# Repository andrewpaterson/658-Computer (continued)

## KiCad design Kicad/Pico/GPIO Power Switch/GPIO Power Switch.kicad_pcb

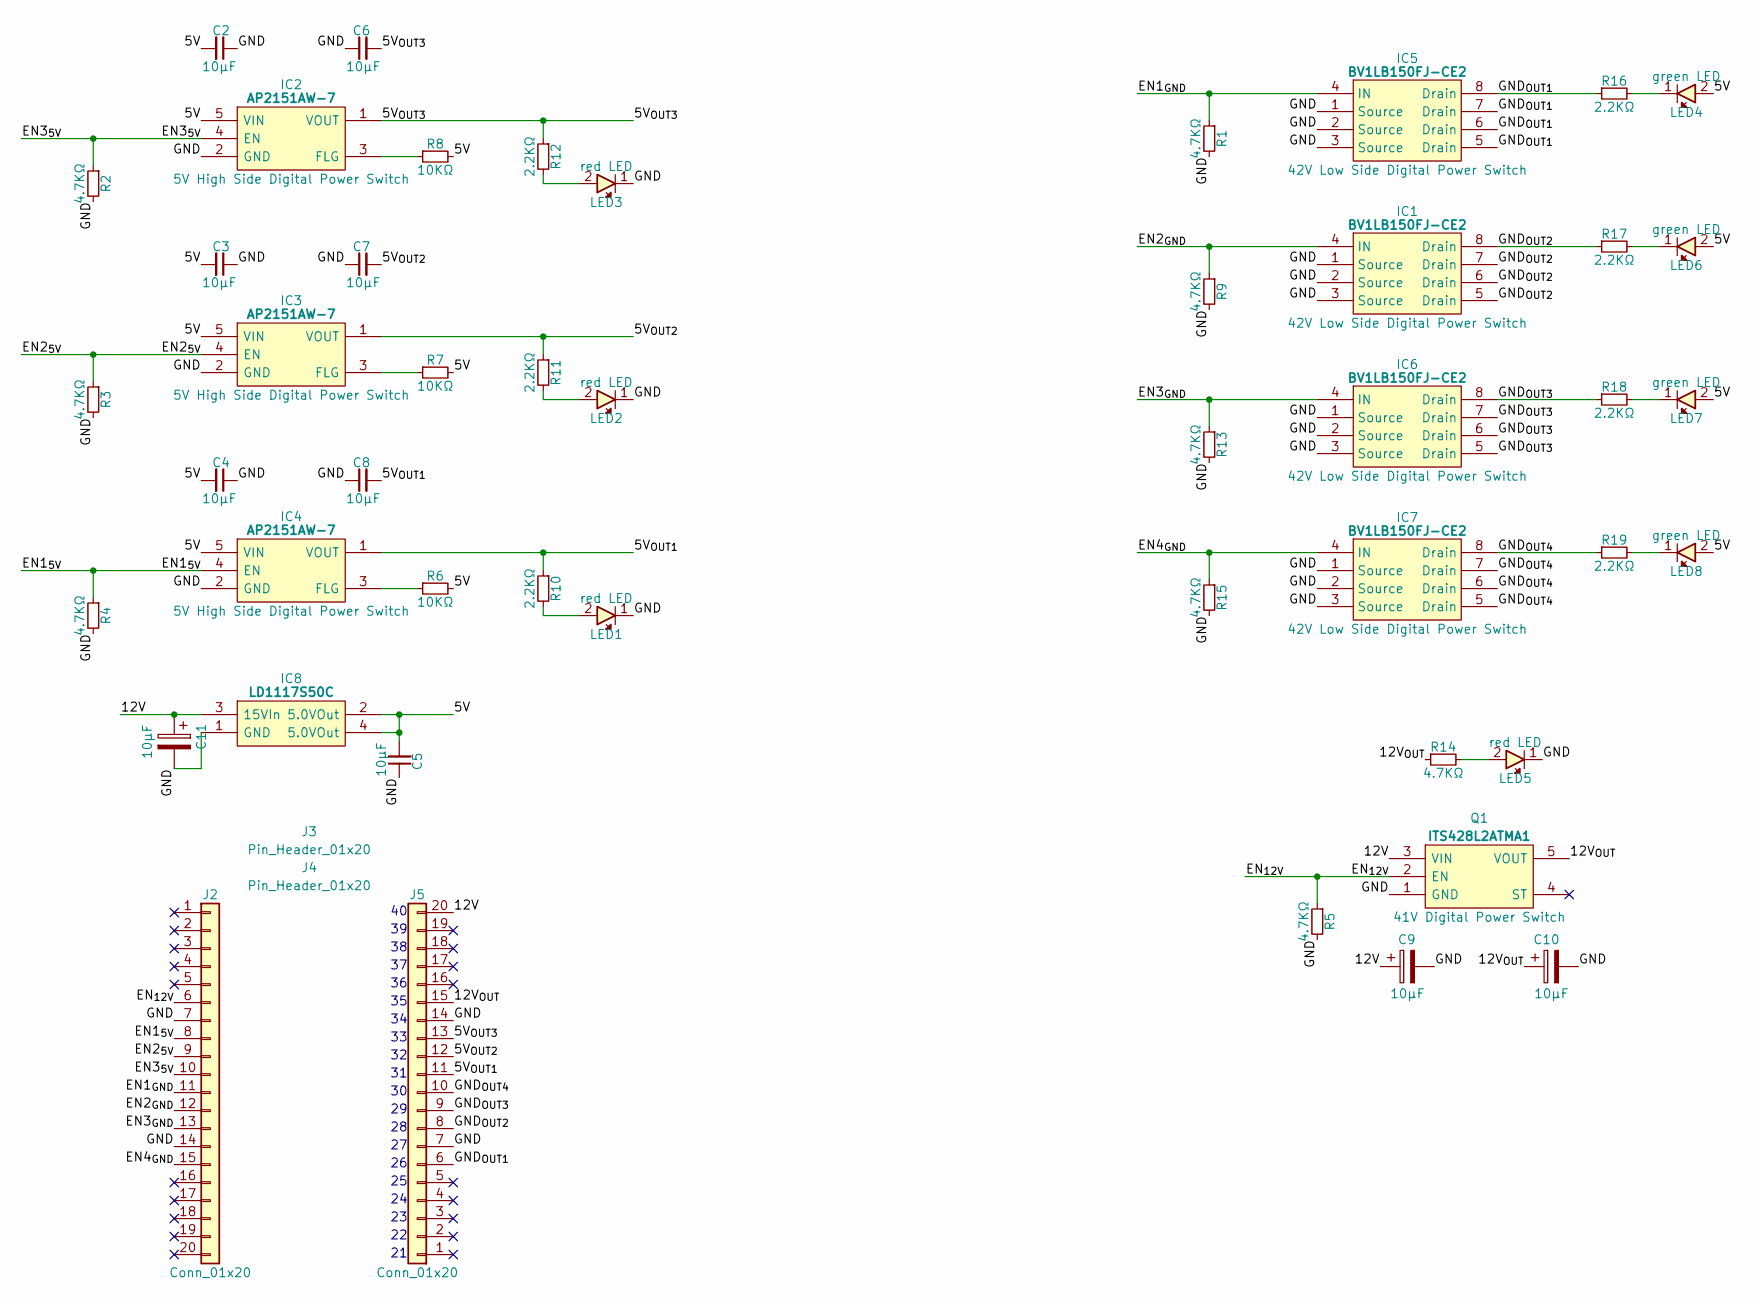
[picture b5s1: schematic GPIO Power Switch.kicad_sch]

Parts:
C2, C3, C4, C5, C6, C7, C8: 10μF; C_0805
C9, C10, C11: 10μF; CP_Radial_D4.0mm_P2.00mm
IC1, IC5, IC6, IC7: BV1LB150FJ-CE2; SOIC127P600X165-8N; Manufacturer_Part_Number BV1LB150FJ-CE2; Mouser Part Number 755-BV1LB150FJ-CE2
IC2, IC3, IC4: AP2151AW-7; SOT95P285X130-5N; Manufacturer_Part_Number AP2151AW-7; Mouser Part Number 621-AP2151AW-7
IC8: LD1117S50C; LD1117S33C; Manufacturer_Part_Number LD1117S50C
J2, J5: Conn_01x20; SIP_20_Pins
J3, J4: Pin_Header_01x20; PinHeader_1x20_P2.54mm_Vertical
LED1, LED2, LED3, LED5: 150224SS73100; 150224SS73100A; Manufacturer_Part_Number 150224SS73100; Mouser Part Number 710-150224SS73100
LED4, LED6, LED7, LED8: 150224VS73100A; Manufacturer_Part_Number 150224VS73100A; Mouser Part Number 710-150224VS73100A
Q1: ITS428L2ATMA1; Manufacturer_Part_Number ITS428L2ATMA1; Mouser Part Number 726-ITS428L2ATMA1
R1, R2, R3, R4, R5, R9, R13, R14, R15: 4.7KΩ; R_0805
R6, R7, R8: 10KΩ; R_0805
R10, R11, R12, R16, R17, R18, R19: 2.2KΩ; R_0805

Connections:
/5V: C2.2, C3.2, C4.2, C5.2, IC2.5 (VIN), IC3.5 (VIN), IC4.5 (VIN), IC8.2 (5.0VOut), IC8.4 (5.0VOut), LED4.2, LED6.2, LED7.2, LED8.2, R6.2, R7.2, R8.2
/5V_{OUT1}: C8.2, IC4.1 (VOUT), J5.11, R10.1
/5V_{OUT2}: C7.2, IC3.1 (VOUT), J5.12, R11.1
/5V_{OUT3}: C6.2, IC2.1 (VOUT), J5.13, R12.1
/12V: C9.1, C11.1, IC8.3 (15VIn), J5.20, Q1.3 (VIN)
/12V_{OUT}: C10.1, J5.15, Q1.5 (VOUT), R14.1
/EN1_{5V}: IC4.4 (EN), J2.8, R4.1
/EN1_{GND}: IC5.4 (IN), J2.11, R1.1
/EN2_{5V}: IC3.4 (EN), J2.9, R3.1
/EN2_{GND}: IC1.4 (IN), J2.12, R9.1
/EN3_{5V}: IC2.4 (EN), J2.10, R2.1
/EN3_{GND}: IC6.4 (IN), J2.13, R13.1
/EN4_{GND}: IC7.4 (IN), J2.15, R15.1
/EN_{12V}: J2.6, Q1.2 (EN), R5.1
/GND: C2.1, C3.1, C4.1, C5.1, C6.1, C7.1, C8.1, C9.2, C10.2, C11.2, IC1.1 (Source), IC1.2 (Source), IC1.3 (Source), IC2.2 (GND), IC3.2 (GND), IC4.2 (GND), IC5.1 (Source), IC5.2 (Source), IC5.3 (Source), IC6.1 (Source), IC6.2 (Source), IC6.3 (Source), IC7.1 (Source), IC7.2 (Source), IC7.3 (Source), IC8.1 (GND), J2.7, J2.14, J5.7, J5.14, LED1.1, LED2.1, LED3.1, LED5.1, Q1.1 (GND), R1.2, R2.2, R3.2, R4.2, R5.2, R9.2, R13.2, R15.2
/GND_{OUT1}: IC5.5 (Drain), IC5.6 (Drain), IC5.7 (Drain), IC5.8 (Drain), J5.6, R16.1
/GND_{OUT2}: IC1.5 (Drain), IC1.6 (Drain), IC1.7 (Drain), IC1.8 (Drain), J5.8, R17.1
/GND_{OUT3}: IC6.5 (Drain), IC6.6 (Drain), IC6.7 (Drain), IC6.8 (Drain), J5.9, R18.1
/GND_{OUT4}: IC7.5 (Drain), IC7.6 (Drain), IC7.7 (Drain), IC7.8 (Drain), J5.10, R19.1
unnamed: IC2.3 (FLG), R8.1
unnamed: IC3.3 (FLG), R7.1
unnamed: IC4.3 (FLG), R6.1
unnamed: LED1.2, R10.2
unnamed: LED2.2, R11.2
unnamed: LED3.2, R12.2
unnamed: LED4.1, R16.2
unnamed: LED5.2, R14.2
unnamed: LED6.1, R17.2
unnamed: LED7.1, R18.2
unnamed: LED8.1, R19.2

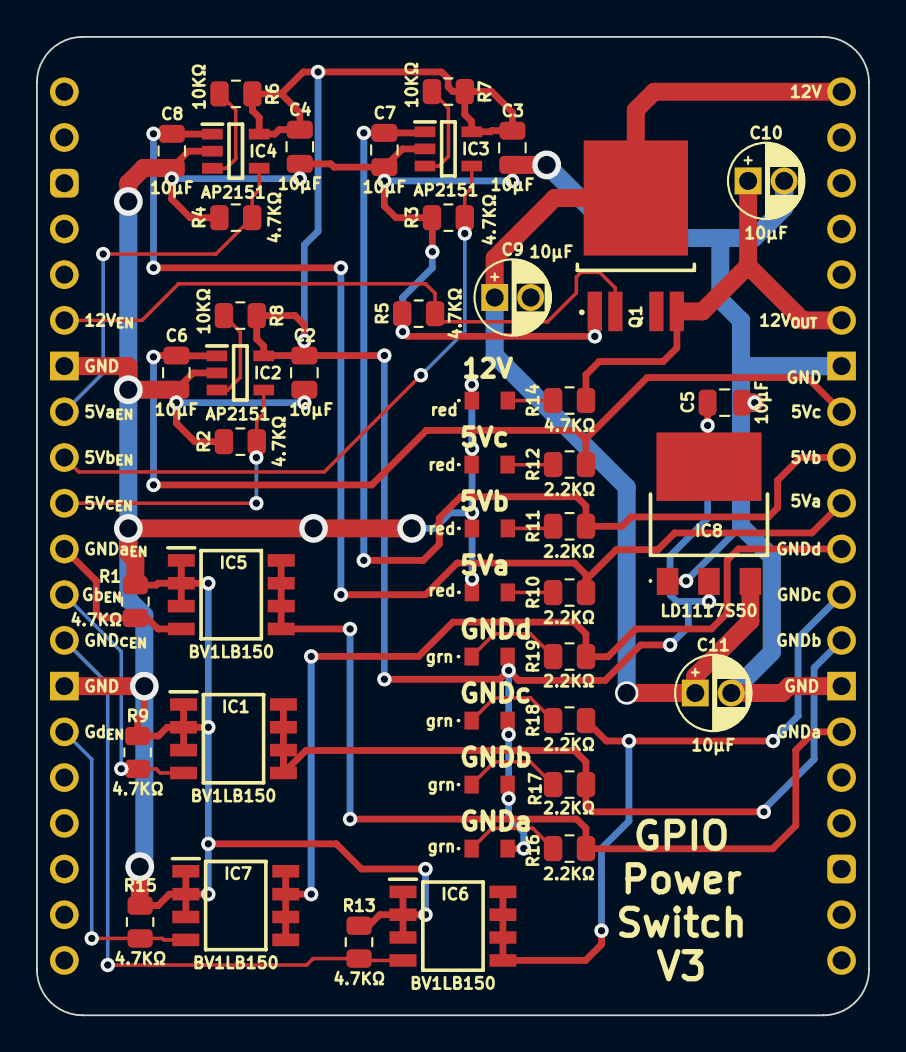
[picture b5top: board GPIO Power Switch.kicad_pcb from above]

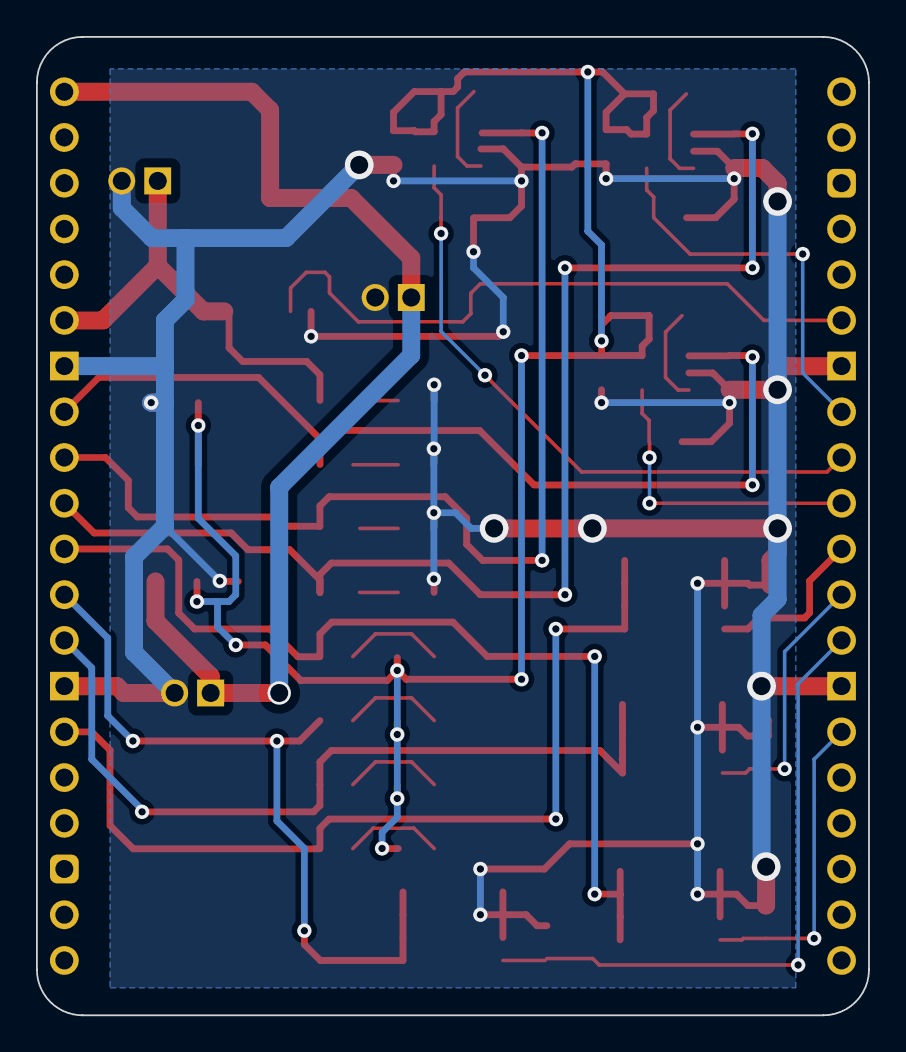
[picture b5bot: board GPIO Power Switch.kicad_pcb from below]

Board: 2 copper layers, 46.2 x 54.4 mm, 50 parts (2 on the bottom side), 30 nets.

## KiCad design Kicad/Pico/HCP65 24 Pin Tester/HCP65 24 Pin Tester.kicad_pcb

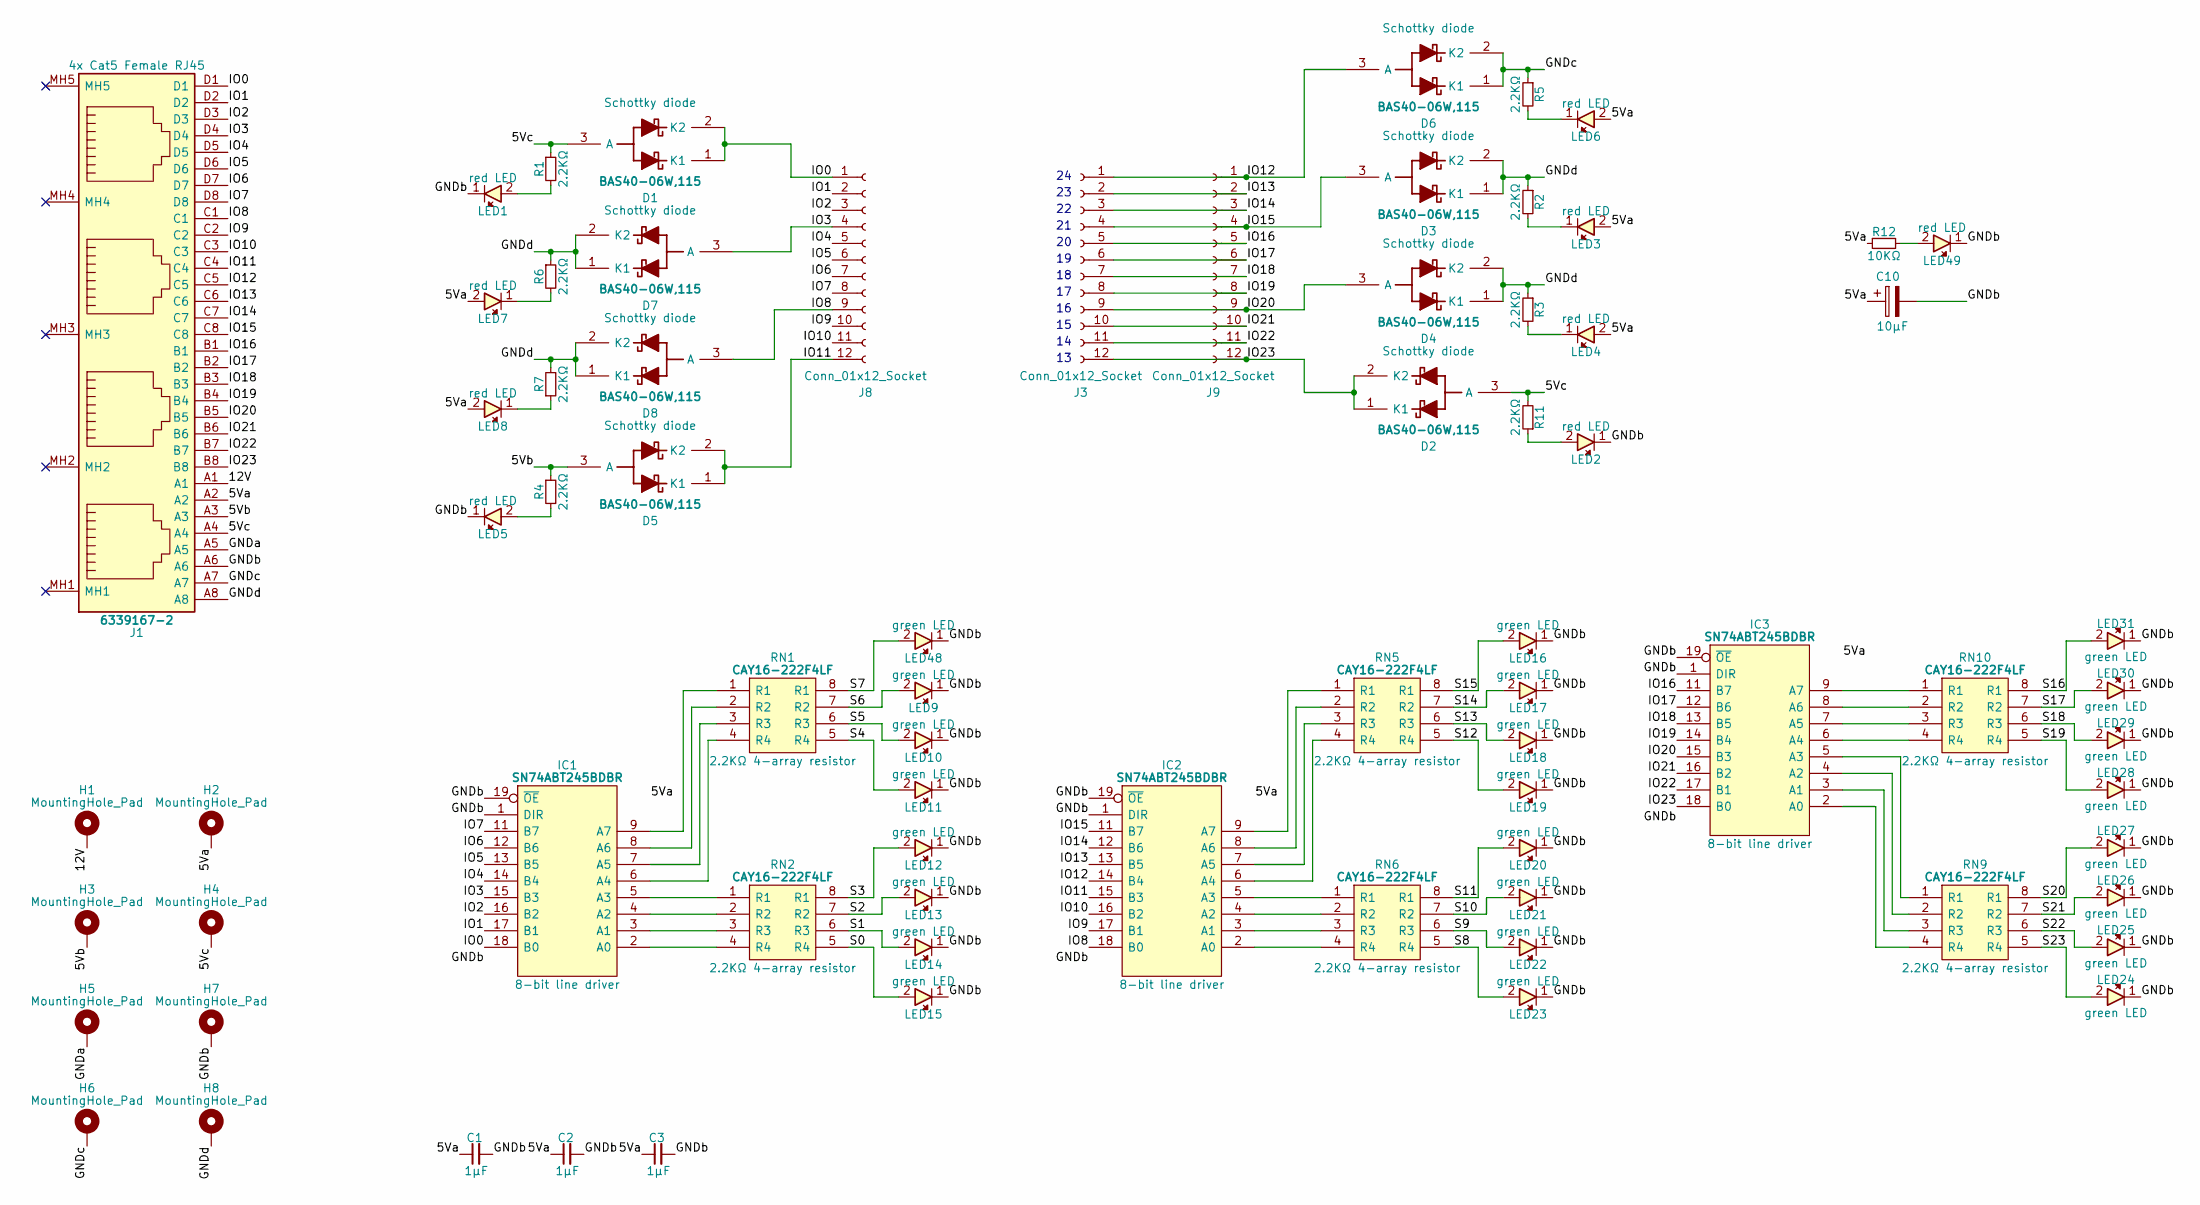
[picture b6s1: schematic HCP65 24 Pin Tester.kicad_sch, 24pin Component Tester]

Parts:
C1, C2, C3: 1μF; C_0805
C10: 10μF; CP_Radial_D4.0mm_P2.00mm
D1, D2, D3, D4, D5, D6, D7, D8: BAS40-06W,115; SOT65P210X110-3N; Manufacturer_Part_Number BAS40-06W,115; Mouser Part Number 771-BAS40-06W115
H1, H2, H3, H4, H5, H6, H7, H8: MountingHole_Pad; MountingHole_3.2mm_M3_Pad
IC1, IC2, IC3: SN74ABT245BDBR; SOP65P780X200-20N; Manufacturer_Part_Number SN74ABT245BDBR; Mouser Part Number 595-SN74ABT245BDBR
J1: 6339167-2; 63391672; Manufacturer_Part_Number 6339167-2; Mouser Part Number 571-6339167-2
J3, J8, J9: Conn_01x12_Socket; PinSocket_1x12_P2.54mm_Vertical
LED1, LED2, LED3, LED4, LED5, LED6, LED7, LED8, LED49: 150224SS73100; 150224SS73100A; Manufacturer_Part_Number 150224SS73100; Mouser Part Number 710-150224SS73100
LED9, LED10, LED11, LED12, LED13, LED14, LED15, LED16, LED17, LED18, LED19, LED20, LED21, LED22, LED23, LED24, LED25, LED26, LED27, LED28, LED29, LED30, LED31, LED48: 150224VS73100A; Manufacturer_Part_Number 150224VS73100A; Mouser Part Number 710-150224VS73100A
R1, R2, R3, R4, R5, R6, R7, R11: 2.2KΩ; R_0805
R12: 10KΩ; R_0805
RN1, RN2, RN5, RN6, RN9, RN10: CAY16-222F4LF; CAY16-J4; Manufacturer_Part_Number CAY16-222F4LF; Mouser Part Number 652-CAY16-2201F4LF

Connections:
/5Va: C1.1, C2.1, C3.1, C10.1, H2.1, IC1.20 (5V), IC2.20 (5V), IC3.20 (5V), J1.A2, LED3.2, LED4.2, LED6.2, LED7.2, LED8.2, R12.1
/5Vb: D5.3 (A), H3.1, J1.A3, R4.1
/5Vc: D1.3 (A), D2.3 (A), H4.1, J1.A4, R1.1, R11.2
/12V: H1.1, J1.A1
/GNDa: H5.1, J1.A5
/GNDb: C1.2, C2.2, C3.2, C10.2, H7.1, IC1.1 (DIR), IC1.10 (GND), IC1.19 (~OE), IC2.1 (DIR), IC2.10 (GND), IC2.19 (~OE), IC3.1 (DIR), IC3.10 (GND), IC3.19 (~OE), J1.A6, LED1.1, LED2.1, LED5.1, LED9.1, LED10.1, LED11.1, LED12.1, LED13.1, LED14.1, LED15.1, LED16.1, LED17.1, LED18.1, LED19.1, LED20.1, LED21.1, LED22.1, LED23.1, LED24.1, LED25.1, LED26.1, LED27.1, LED28.1, LED29.1, LED30.1, LED31.1, LED48.1, LED49.1
/GNDc: D6.1 (K1), D6.2 (K2), H6.1, J1.A7, R5.1
/GNDd: D3.1 (K1), D3.2 (K2), D4.1 (K1), D4.2 (K2), D7.1 (K1), D7.2 (K2), D8.1 (K1), D8.2 (K2), H8.1, J1.A8, R2.1, R3.1, R6.1, R7.2
/IO0: D1.1 (K1), D1.2 (K2), IC1.18 (B0), J1.D1, J8.1
/IO1: IC1.17 (B1), J1.D2, J8.2
/IO2: IC1.16 (B2), J1.D3, J8.3
/IO3: D7.3 (A), IC1.15 (B3), J1.D4, J8.4
/IO4: IC1.14 (B4), J1.D5, J8.5
/IO5: IC1.13 (B5), J1.D6, J8.6
/IO6: IC1.12 (B6), J1.D7, J8.7
/IO7: IC1.11 (B7), J1.D8, J8.8
/IO8: D8.3 (A), IC2.18 (B0), J1.C1, J8.9
/IO9: IC2.17 (B1), J1.C2, J8.10
/IO10: IC2.16 (B2), J1.C3, J8.11
/IO11: D5.1 (K1), D5.2 (K2), IC2.15 (B3), J1.C4, J8.12
/IO12: D6.3 (A), IC2.14 (B4), J1.C5, J3.1, J9.1
/IO13: IC2.13 (B5), J1.C6, J3.2, J9.2
/IO14: IC2.12 (B6), J1.C7, J3.3, J9.3
/IO15: D3.3 (A), IC2.11 (B7), J1.C8, J3.4, J9.4
/IO16: IC3.11 (B7), J1.B1, J3.5, J9.5
/IO17: IC3.12 (B6), J1.B2, J3.6, J9.6
/IO18: IC3.13 (B5), J1.B3, J3.7, J9.7
/IO19: IC3.14 (B4), J1.B4, J3.8, J9.8
/IO20: D4.3 (A), IC3.15 (B3), J1.B5, J3.9, J9.9
/IO21: IC3.16 (B2), J1.B6, J3.10, J9.10
/IO22: IC3.17 (B1), J1.B7, J3.11, J9.11
/IO23: D2.1 (K1), D2.2 (K2), IC3.18 (B0), J1.B8, J3.12, J9.12
/S0: LED15.2, RN2.5 (R4)
/S1: LED14.2, RN2.6 (R3)
/S2: LED13.2, RN2.7 (R2)
/S3: LED12.2, RN2.8 (R1)
/S4: LED11.2, RN1.5 (R4)
/S5: LED10.2, RN1.6 (R3)
/S6: LED9.2, RN1.7 (R2)
/S7: LED48.2, RN1.8 (R1)
/S8: LED23.2, RN6.5 (R4)
/S9: LED22.2, RN6.6 (R3)
/S10: LED21.2, RN6.7 (R2)
/S11: LED20.2, RN6.8 (R1)
/S12: LED19.2, RN5.5 (R4)
/S13: LED18.2, RN5.6 (R3)
/S14: LED17.2, RN5.7 (R2)
/S15: LED16.2, RN5.8 (R1)
/S16: LED31.2, RN10.8 (R1)
/S17: LED30.2, RN10.7 (R2)
/S18: LED29.2, RN10.6 (R3)
/S19: LED28.2, RN10.5 (R4)
/S20: LED27.2, RN9.8 (R1)
/S21: LED26.2, RN9.7 (R2)
/S22: LED25.2, RN9.6 (R3)
/S23: LED24.2, RN9.5 (R4)
unnamed: IC1.2 (A0), RN2.4 (R4)
unnamed: IC1.3 (A1), RN2.3 (R3)
unnamed: IC1.4 (A2), RN2.2 (R2)
unnamed: IC1.5 (A3), RN2.1 (R1)
unnamed: IC1.6 (A4), RN1.4 (R4)
unnamed: IC1.7 (A5), RN1.3 (R3)
unnamed: IC1.8 (A6), RN1.2 (R2)
unnamed: IC1.9 (A7), RN1.1 (R1)
unnamed: IC2.2 (A0), RN6.4 (R4)
unnamed: IC2.3 (A1), RN6.3 (R3)
unnamed: IC2.4 (A2), RN6.2 (R2)
unnamed: IC2.5 (A3), RN6.1 (R1)
unnamed: IC2.6 (A4), RN5.4 (R4)
unnamed: IC2.7 (A5), RN5.3 (R3)
unnamed: IC2.8 (A6), RN5.2 (R2)
unnamed: IC2.9 (A7), RN5.1 (R1)
unnamed: IC3.2 (A0), RN9.4 (R4)
unnamed: IC3.3 (A1), RN9.3 (R3)
unnamed: IC3.4 (A2), RN9.2 (R2)
unnamed: IC3.5 (A3), RN9.1 (R1)
unnamed: IC3.6 (A4), RN10.4 (R4)
unnamed: IC3.7 (A5), RN10.3 (R3)
unnamed: IC3.8 (A6), RN10.2 (R2)
unnamed: IC3.9 (A7), RN10.1 (R1)
unnamed: LED1.2, R1.2
unnamed: LED2.2, R11.1
unnamed: LED3.1, R2.2
unnamed: LED4.1, R3.2
unnamed: LED5.2, R4.2
unnamed: LED6.1, R5.2
unnamed: LED7.1, R6.2
unnamed: LED8.1, R7.1
unnamed: LED49.2, R12.2

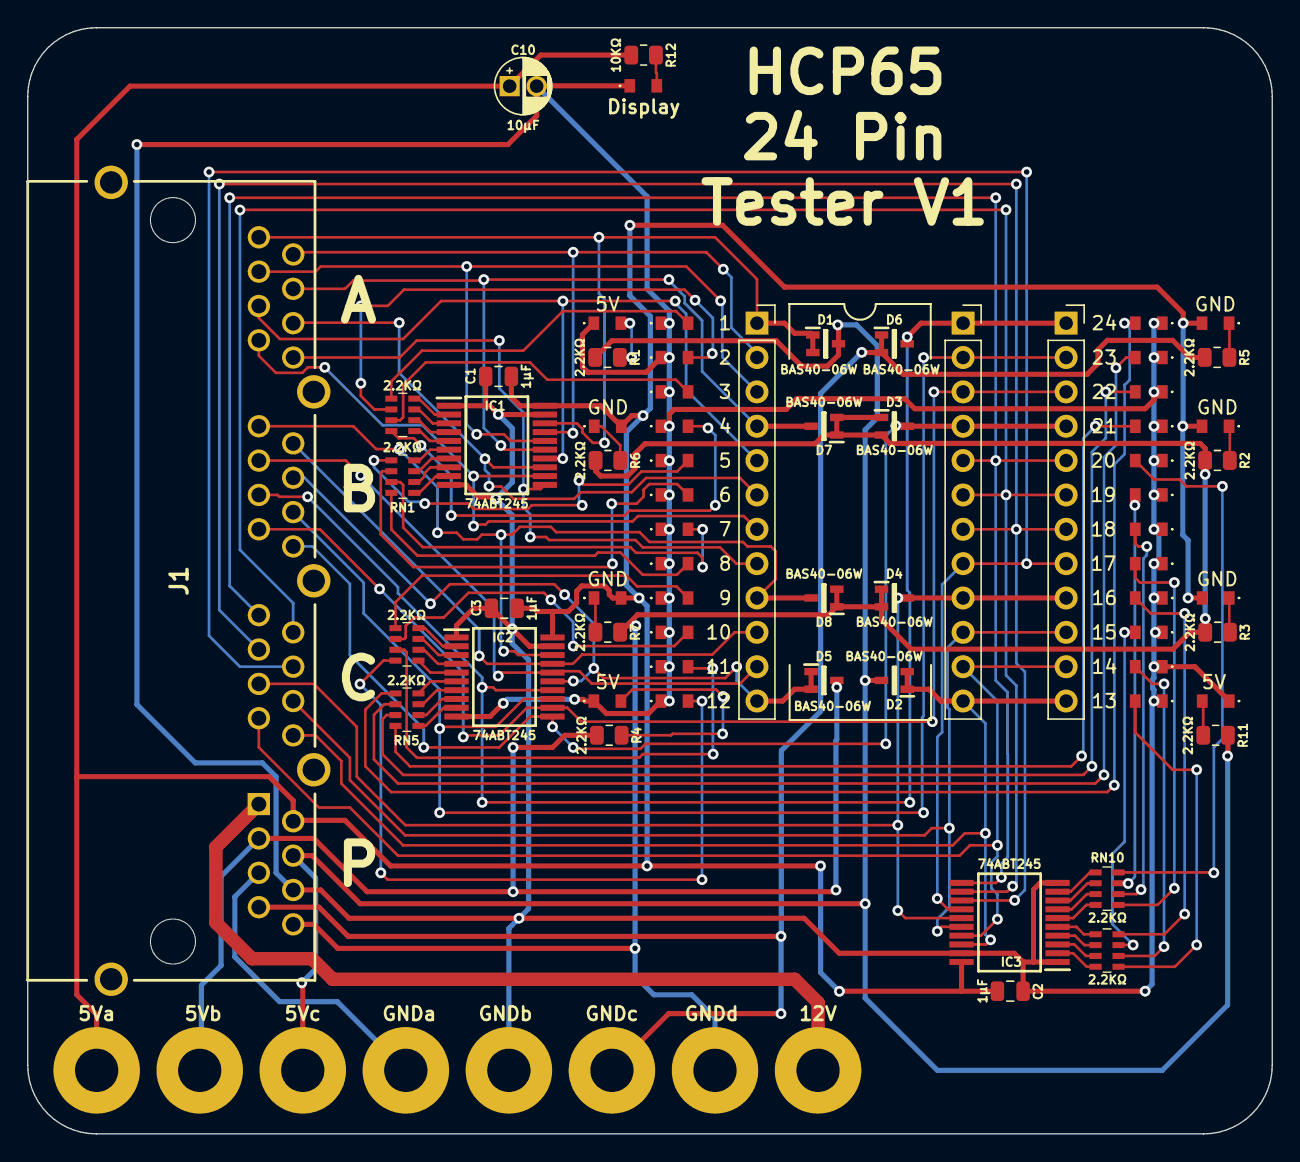
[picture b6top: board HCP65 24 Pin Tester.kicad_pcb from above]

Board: 2 copper layers, 92.0 x 81.8 mm, 75 parts (0 on the bottom side), 89 nets.
